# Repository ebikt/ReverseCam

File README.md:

USB Reverse Camera
==================

Q: Why? \
A: I don't want to install another screen to my car. Just use my phone or tablet.

Q: Why not just connect the wires? \
A1: Typical Android does not charge in USB Host mode. \
A2: Android 11 has bug, that displays popup whenever camera application is triggered by attaching USB Video Grabber card.

Disclaimer
----------

I have no proper education in electronics! I just use transistors "the digital way" and hope that all currents
and voltages are within limits. I used ngspice to verify my ideas before trying to build the circuits in real
world. That means, that the circuit may be unreliable as I did not check that there are enough operational
margins.

Switching between USB Host and Charging
---------------------------------------

USB C has special wire, that governs who is charning and who is charged. Android uses this also to decide who controls
the bus. This is pure analog signal, just a resistor connected to either ground or 5V. So we switch it when we want to
go from charging mode to USB Host mode and back. This can be done using relay as seen below. This was my proof of
concept and worked with my Android 11 Nokia phone.

Warning! This wiring has one caveat, it does not disconnect data lines, thus fast charging may
or may not work with your device. My device fast-charged reliably using
[this charger](https://www.pselectronic.cz/k5503-5097-hm113-menic-dcdc-6-24v5v-3a-usb.html)
only if the electronic version of relay (second image) was switched to USB Host mode for more that 30 seconds.
I did not perform any thorough tests with physical relay.

But I don't like relays (they draw too much current for my taste). Thus I replaced the relay with transistors:

Dealing with popup when reversing into tight spot
-------------------------------------------------

Simple solution would be just having switch on dashboard, and send 12V to camera from that switch by wire to
the camera itself. But then I would be stuck with this switch also on other Androids that do not have that bug.
On the other hand, triggering switch and confirming popup **just once** per reverse maneuver is same amount of work.
So we just need to not detach camera in multi-stage reverse maneuver. This can be achieved by delaying shutdown
of camera by one minute, or similar interval:

Simulations in KiCad + ngspice
------------------------------

I used KiCad 6.0 to draw schematics and downloaded
[Kicad-Spice-Library](https://github.com/kicad-spice-library/KiCad-Spice-Library)
to be able to specify parameters for simulation.
Run `git clone https://github.com/kicad-spice-library/KiCad-Spice-Library` in root of working tree, to
enable simulations in KiCad+ngspice.

Which usb card? Which Android app? Which USB-C Cable?
-----------------------------------------------------

App: [nExt Camera - USB](https://play.google.com/store/apps/details?id=pl.nextcamera) works great with UTV007 cards

Camera: UTV007 card, e.g. [Gemird UVG-002](https://www.mironet.cz/gembird-uvg002-cerna-video-capturing-device-s-programovanim-tv-fm-usb+dp516087/)

Cable: interconnecting USB-C cable - for these to work, there must be fifth wire in the cable, which is used
by Android to detect if other end is a power bank, or some peripheral device that needs to be powered from
battery of the Android device. Simply cut off one of the connectors.

Alternative fast charging wiring
--------------------------------

If you have problem with fast-charging use 4-pole relay (or two 2-pole relays, timing is not so crucial here),
the two additional poles will disconnect data wires from usb-host. It may also help if it connects D+ and D-
of the smartphone together when charging. Some (old) devices used this to detect charger.

Remarks
-------

Similar things may apply to handhelds with other operating systems, because principles of USB are not software
specific. Although there is no hardware obstacle for mixed mode (controlling USB Bus, while being charged),
drivers (both software and hardware) in devices typically do not implement this mode, as there are very
few customers that will pay for it. That means less unexpected behaviour and less testing and bugfixing
for hardware vendors.

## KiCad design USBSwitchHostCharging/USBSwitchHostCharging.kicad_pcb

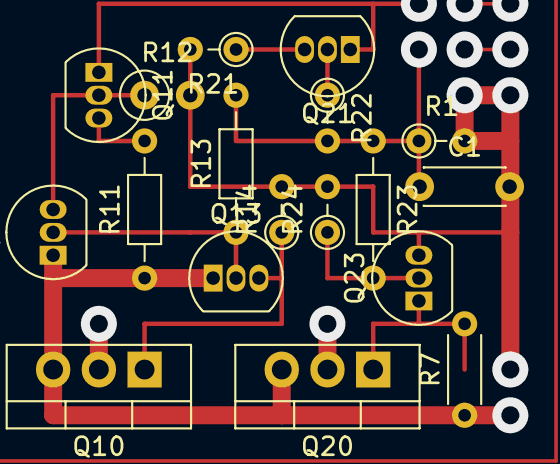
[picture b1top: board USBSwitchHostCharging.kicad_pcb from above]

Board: 2 copper layers, 18 parts (0 on the bottom side), 12 nets.

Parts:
C1: 1n; C_Disc_D4.3mm_W1.9mm_P5.00mm
Q10, Q20: IRF4905; TO-220-3_Vertical
Q11: BC557C; TO-92_Inline
Q12, Q13, Q21, Q23: BC548C; TO-92_Inline
R1: 10k; R_Axial_DIN0204_L3.6mm_D1.6mm_P2.54mm_Vertical
R7: 1000k; R_Axial_DIN0204_L3.6mm_D1.6mm_P5.08mm_Horizontal
R11: 56k; R_Axial_DIN0204_L3.6mm_D1.6mm_P7.62mm_Horizontal
R12: 1000k; R_Axial_DIN0207_L6.3mm_D2.5mm_P2.54mm_Vertical
R13, R23: 1000k; R_Axial_DIN0204_L3.6mm_D1.6mm_P7.62mm_Horizontal
R14, R22: 1000k; R_Axial_DIN0204_L3.6mm_D1.6mm_P2.54mm_Vertical
R21: 15k; R_Axial_DIN0204_L3.6mm_D1.6mm_P2.54mm_Vertical
R24: 220k; R_Axial_DIN0204_L3.6mm_D1.6mm_P2.54mm_Vertical

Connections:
+5V: Q10.3 (S), Q12.1 (C), Q13.1 (C), Q20.3 (S), R7.1, R11.1
/SW_Charge: Q12.2 (B), Q13.2 (B), R13.1
/SW_host: Q23.2 (B), R23.2, R24.1
GND: C1.2, Q23.3 (E), R1.2, R12.2, R14.2, R21.2, R24.2
unnamed: Q10.1 (G), Q13.3 (E), R14.1
unnamed: Q11.2 (B), Q12.3 (E), R12.1
unnamed: Q11.3 (E), R11.2
unnamed: Q20.1 (G), Q23.1 (C), R7.2
unnamed: Q21.2 (B), R22.1
unnamed: Q21.3 (E), R21.1
PD Sense: Q11.1 (C), Q21.1 (C)
Switch: C1.1, R1.1, R13.2, R22.2, R23.1

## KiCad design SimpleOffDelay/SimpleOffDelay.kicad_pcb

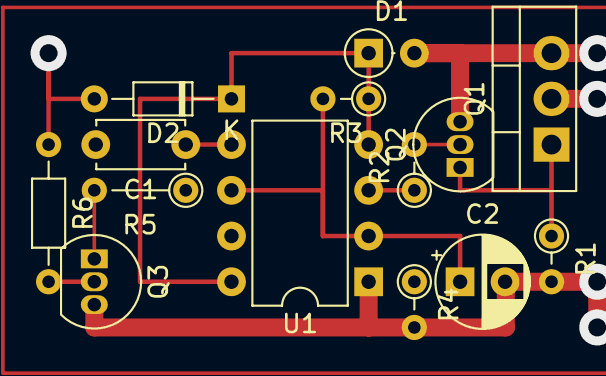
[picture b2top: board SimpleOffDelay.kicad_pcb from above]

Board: 2 copper layers, 14 parts (0 on the bottom side), 11 nets.

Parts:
C1: 10n; C_Disc_D4.7mm_W2.5mm_P5.00mm
C2: 470u; CP_Radial_D5.0mm_P2.50mm
D1: 1N4148; D_DO-35_SOD27_P2.54mm_Vertical_AnodeUp
D2: 1N4148; D_DO-34_SOD68_P7.62mm_Horizontal
Q1: IRF4905; TO-220-3_Vertical
Q2: BC557C; TO-92_Inline
Q3: BC548; TO-92_Inline
R1, R2: 470k; R_Axial_DIN0204_L3.6mm_D1.6mm_P2.54mm_Vertical
R3: 100k; R_Axial_DIN0204_L3.6mm_D1.6mm_P2.54mm_Vertical
R4: 1Meg; R_Axial_DIN0204_L3.6mm_D1.6mm_P2.54mm_Vertical
R5: 100; R_Axial_DIN0204_L3.6mm_D1.6mm_P5.08mm_Vertical
R6: 100k; R_Axial_DIN0204_L3.6mm_D1.6mm_P7.62mm_Horizontal
U1: ICM7555xP; DIP-8_W7.62mm

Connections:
+12V: D1.2 (A), Q1.3 (S), Q2.3 (E)
/Charge: C2.1, R3.2, R4.1, R5.1, U1.2 (TR), U1.6 (THR)
/On: R2.1, U1.3 (Q)
/Vcc: D1.1 (K), D2.1 (K), R3.1, U1.4 (R), U1.8 (VCC)
GND: C1.2, C2.2, Q3.3 (E), R1.2, R4.2, U1.1 (GND)
In: D2.2 (A), R6.1
unnamed: C1.1, U1.5 (CV)
unnamed: Q1.1 (G), Q2.1 (C), R1.1
unnamed: Q2.2 (B), R2.2
unnamed: Q3.1 (C), R5.2
unnamed: Q3.2 (B), R6.2

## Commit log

2022-09-09 schematics
2022-09-09 Documentation.
2022-09-09 Hand edit svg dimensions and background.
2022-09-09 Fix relay schematics.
2022-09-09 English.
2022-09-09 Force github to invalidate cache.
2022-09-09 Fix Relay.svg wiring.
2022-09-09 Replace alternative wiring section. PDSense cannot be ommited.
